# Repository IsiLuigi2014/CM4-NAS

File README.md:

# CM4 NAS Board [UNMAINTAINED | UNTESTED]

This is a fork from the CM4 NAS Board Project from mebs, added 12V power circuitry only to power it. UNTESTED

This Compute Module 4 carrier board design exposes a subset of the CM4's interfaces, including its single PCIe 2.0 lane to accept an external SATA controller card.
This design is based off of the official Raspberry Pi Foundation's CM4 IO board (the KiCad project is available on the [IO board official page](https://www.raspberrypi.org/products/compute-module-4-io-board/?resellerType=home)). Removed the IO that was less relevant for a NAS and rearranged the remaining interfaces for a smaller footprint that would fit within the width of a standard 3.5" hard drive.

The board was intentionally kept simple to limit mistakes as this is my first ever attempt at designing a PCB and I have no background in electronics, so all the power management is left to external power supplies and buck converters. It's important to use good quality regulated power supplies with this board as it offers no protection other than what is built into the CM4.

Also made 3D printed enclosure for the final product. Design available here: https://www.thingiverse.com/thing:4820662 (Properly not compertablie anymore since made board bigger for 12v power only)

Feel free to explore the discussion section of this repo to share ideas.

[Latest Reddit post here.](https://www.reddit.com/r/raspberry_pi/comments/mkbxss/cm4_custom_nas_complete/)

##### Table of Contents
- [Software](#software)
- [Board IO](#board-io)
  * [CM4 IO Breakout](#cm4-io-breakout)
  * [Other Connections on the Board](#other-connections-on-the-board)
- [PCB Assembly](#pcb-assembly)
  * [Manufacturing](#manufacturing)
  * [Required Parts](#required-parts)
  * [Building](#building)
- [Pinout](#pinout)
- [Revision History](#revision-history)

# Software
For the software part of this project, I highly recommend [Jeff Geerling's repo](https://github.com/geerlingguy/raspberry-pi-pcie-devices/issues), where he documented similar endeavors, but you will likely have to recompile the kernel after enabling some modules to be able to use a PCIe SATA controller.

Don't hesitate to ask questions in the Discussion tab of this repo.

# Board IO
## CM4 IO Breakout
The interfaces the board forwards from the CM4 are the following:
- **PCIe x1 Gen2**: Good old PCIe 2.0, nothing special about it... if not that it's on a Raspberry Pi.
- **Ethernet**: To reduce the number of components on the board and make assembly easier, a MagJack is used instead of a simple RJ45 connector. I had to look this up when I saw it in the IO board design, but a MagJack seems to be simply an RJ45 connector with integrated filters to help with signal integrity. Footprint is specific to the part listed bellow.
- **Single master/slave USB, selected with jumper**: A USB type A port to plug a keyboard, a flash drive, a hub, or whatever you want to use as a USB slave to the CM4. Footprint is not standard so make sure it fits yours if you manufacture the PCB. Can also be used in slave mode (CM4 as slave). You would use this to program the eMMC with you computer. This connection taps into the same single USB bus the CM4 has to offer, but when this is used, the VCC input from the master signals that the CM4 should behave as a slave. Currently the footprint for this is a simple 5 pin header.
- **Full size HDMI**:  Mostly for debugging purposes, hooked to the HDMI0 output of the CM4.
- **I²C**: This is marked "OLED" on the board because this was the intended use, but you can use this to slave any I²C device to the CM4. Five-pin JST connector footprint (fits simple headers too).
- **Single wire temperature sensor**: Marked "Temp_sensor" on the board, hooked to GPIO_4 on the CM4. I would recommend using it for a temp sensor near the SATA controller because they can get really hot and control the fan (see bellow) based on that.
- **9 GPIOs**: General purpose IO header, including Gnd, 3V3 and 5V pins.
- **Configuration headers**: nRPIBOOT, EEPROM_nWP, AIN1, SYNC_IN, SYNC_OUT, TV_OUT, GLOBAL_EN, RUN_PG, WL_nDis, BT_nDis. The pinout is detailed on the board.

## Other Connections on the Board
Other than relaying the compute module's IOs, the board adds other connections, mainly for power.
- **Fan control**: The board expects a dedicated PWM fan controller IC (see part list). Its output is routed to this JST connector (or your typical PWM fan connector) marked "Fan_PWM" on the board.
- **USB selection headers**: To avoid needing a USB MUX on board, this header should be used with a jumper to select if you want to use the USB bus as master or as slave.
- **HDDs power**: Labeled "SATA_PWR". This is the power rail for the hard drives.

# PCB Assembly
## Manufacturing
There is a *Fab* folder at the repo's root. This folder contains all the files that you need to order PCBs from a manufacturer. You will find in the folder a Fab_rev1.4.zip archive that is all you need to order from JLC PCB. This is the latest version and the one I have been running for months now.

## Required Parts
Other than the standard caps and resistors, here are the components you will need if you want to assemble the board:
- **High density connectors** ([digikey](https://www.digikey.ca/en/products/detail/hirose-electric-co-ltd/DF40C-100DS-0.4V%2851%29/1969495), [LCSC](https://lcsc.com/product-detail/Mezzanine-Connectors-Board-to-Board_HRS-Hirose-DF40C-100DS-0-4V-51_C597931.html)): You will need these to connect the CM4 to the board. They can be very daunting, but I found [this video](https://www.youtube.com/watch?v=eukcrFc18P4) of someone neatly soldering them with a hot air gun. When I finaly got to try it, I was surprise at how doable it was.
- **Ethernet** ([digikey](https://www.digikey.de/de/products/detail/abracon-llc/ARJM11C7-502-AB-ER2-T/7675199)): Switch from the expensive one to a cheaper model.
- **Fan controller** ([digikey](https://www.digikey.ca/en/products/detail/microchip-technology/EMC2301-1-ACZL-TR/4696431), [LCSC](https://lcsc.com/product-detail/_MICROCHIP_EMC2301-1-ACZL-TR_EMC2301-1-ACZL-TR_C148036.html)): This chip is the exact same one that is on the official IO board and it's controlled by the CM4 through I²C.
- **ESD sinks** ([digikey](https://www.digikey.ca/en/products/detail/texas-instruments/TPD4EUSB30DQAR/2503671), [LCSC](https://lcsc.com/product-detail/Diodes-ESD_Texas-Instruments-TPD4EUSB30DQAR_C90627.html)): They are optional in my (very uninformed) opinion. I think they were included on the IO board for POE applications mostly.
- **Signal buffer** ([digikey](https://www.digikey.ca/en/products/detail/diodes-incorporated/74LVC1G07SE-7/2356550), [LCSC](https://lcsc.com/product-detail/Logic-Buffers-Drivers-Receivers-Transceivers_Diodes-Incorporated-74LVC1G07SE-7_C67531.html)): Used for the power LED and to buffer RUN_PG signal to be able to wake the CM4 from a sleep state.
- **HDMI connector** ([LCSC](https://lcsc.com/product-detail/Audio-Video-Connectors_SOFNG-HDMI-019S_C111617.html)): Basic full size HDMI connector.

## Building
To build the board, you will need a soldering iron and a hot air gun (or a reflow oven). I would recommend starting with the Hirose high density connectors as they are without a doubt the hardest part. [This video](https://www.youtube.com/watch?v=eukcrFc18P4) I referred to earlier is a good starting point, it makes for a fine tutorial.
It only took a couple tries before I could get a decent result (image from microscope at around 50-60x):

Once the HD connectors are in place, you can move on to the ESD sinks. They are very small and can also be daunting, but soldering them turned out to be easier than expected.
The trick is to put as little solder paste as possible and the chips will naturally be pulled in place by the solder's surface tension.

The rest of the parts should be fairly easy to solder with a standard iron.

# Pinout
**Not up to date anymore.**

# Revision History
- **1**: Initial version
- **1.1**: Fixed wrong footprint for fan controller
- **1.2**: Changed the USB select headers for a simpler solution with a single jumper
- **1.3**: Replaced the HDMI header by a full size HDMI female connector, exposed 9 GPIOs, inverted polarity back for PCIe Tx/Rx signals and added a power LED.
- **1.4**: Add pin to OLED connector for button, use SMD caps and LEDs, more info on silkscreen and fixed some traces.
- **1.5**: Added support for 12v power only

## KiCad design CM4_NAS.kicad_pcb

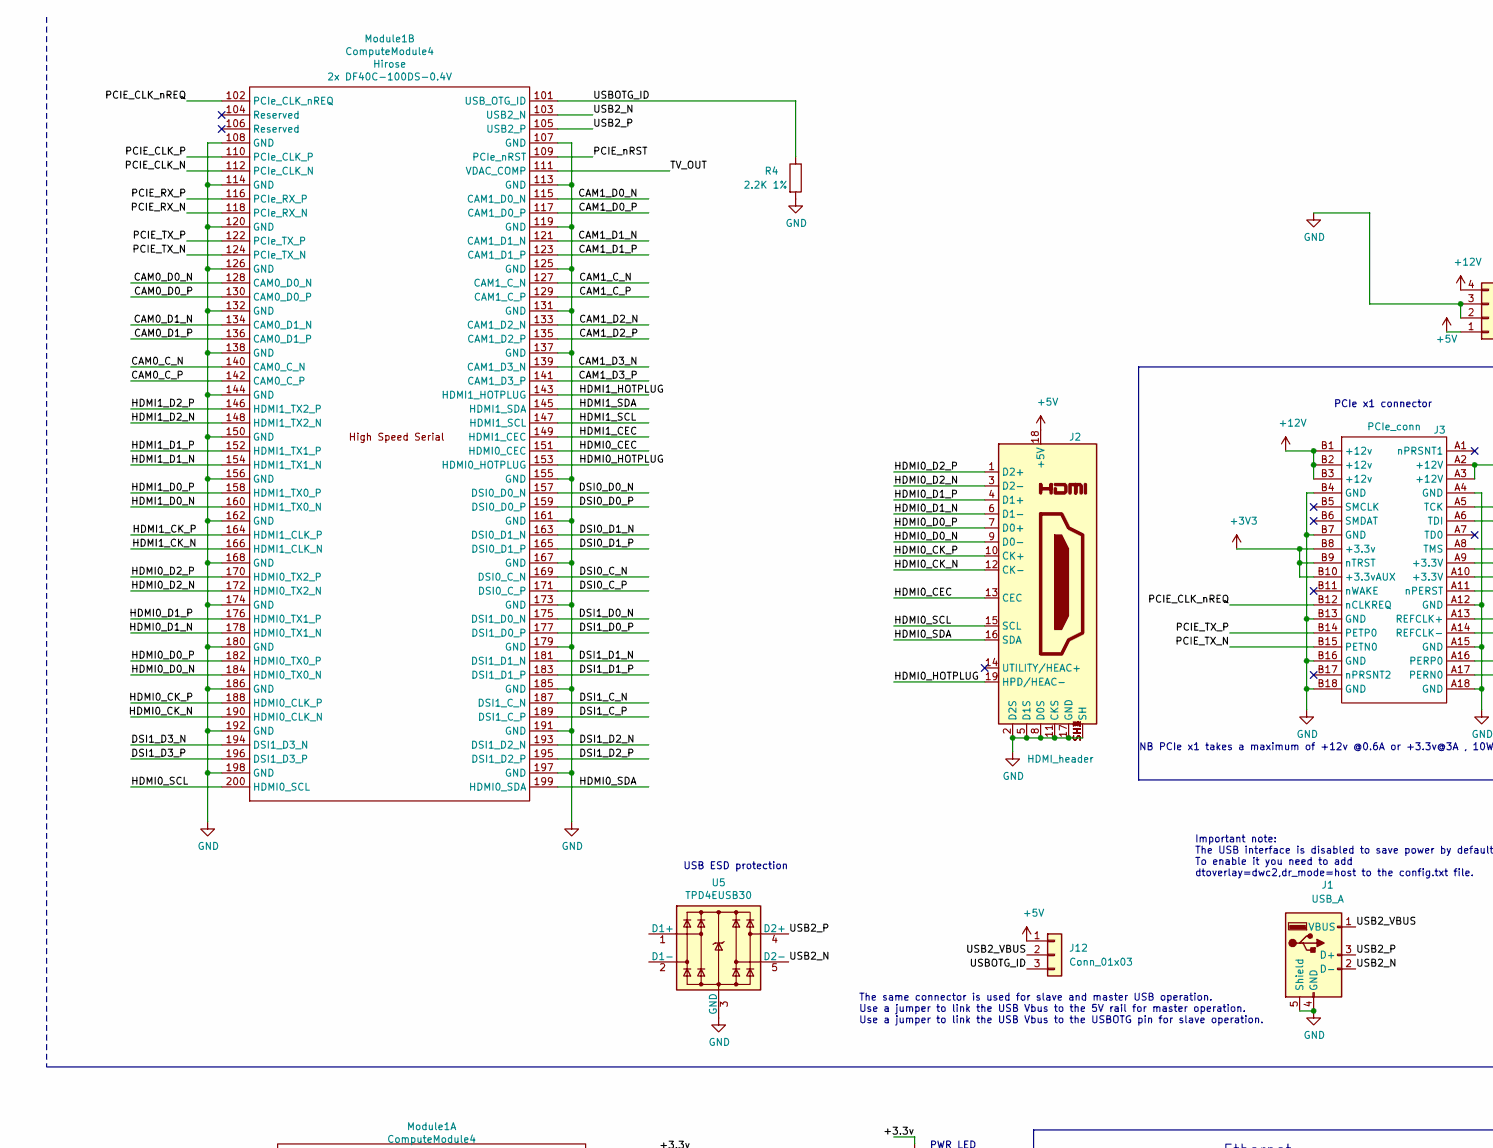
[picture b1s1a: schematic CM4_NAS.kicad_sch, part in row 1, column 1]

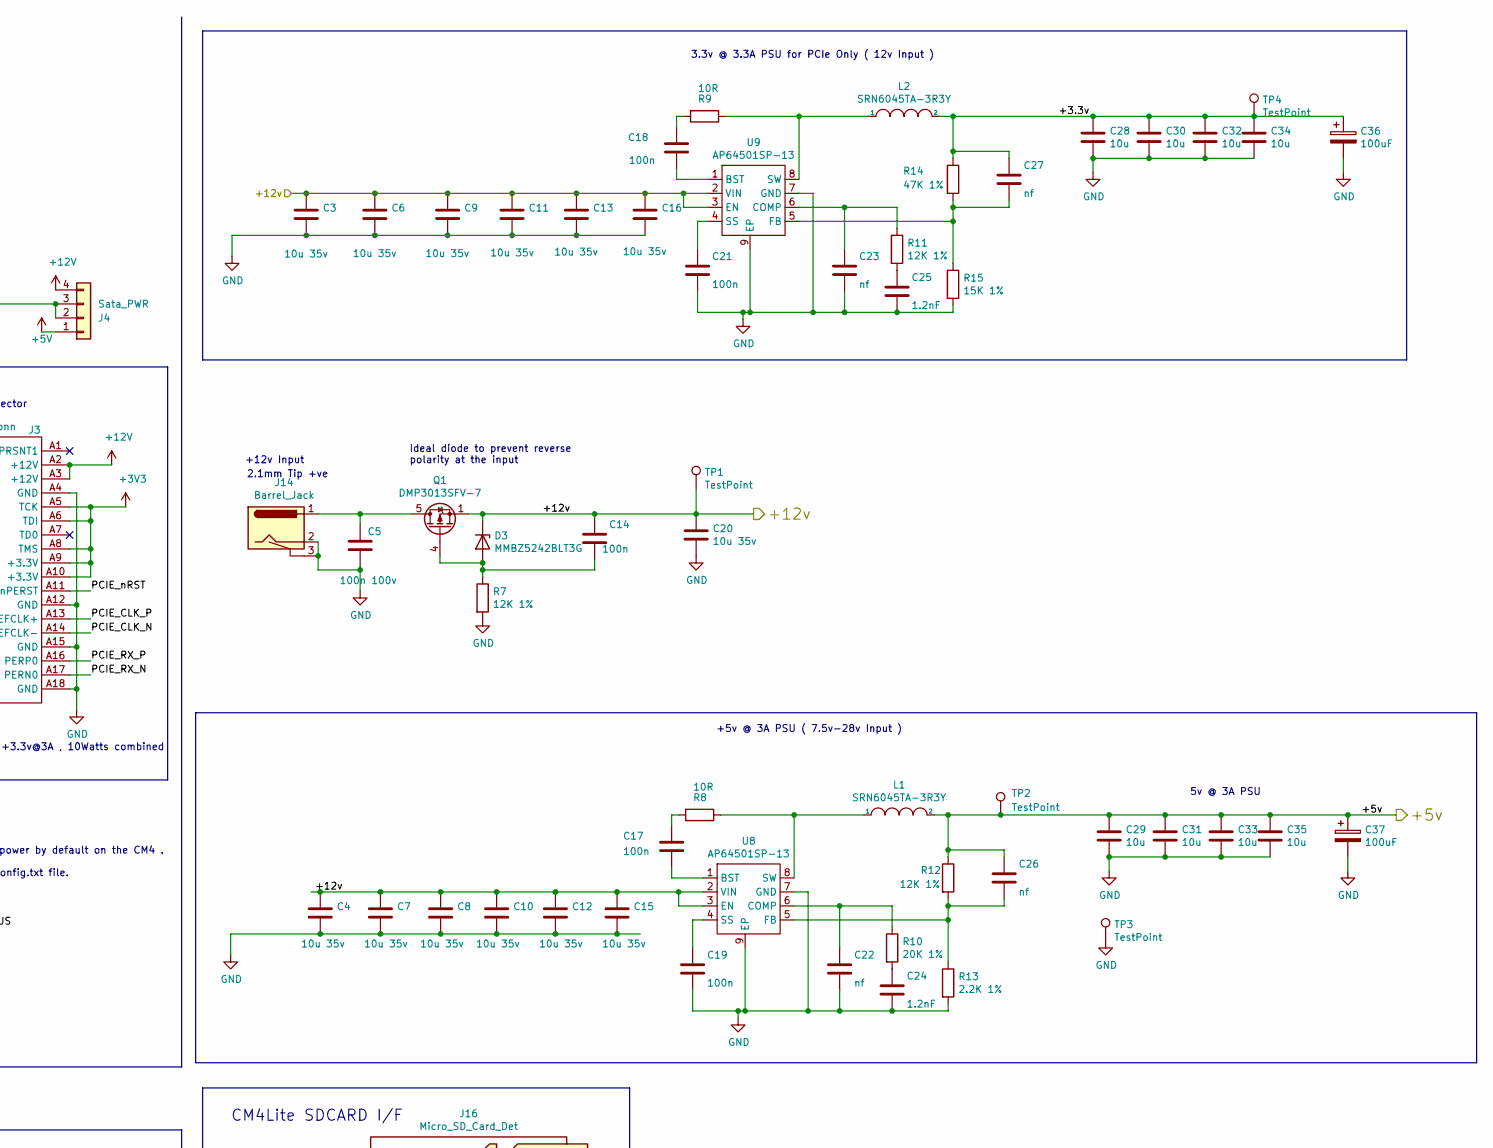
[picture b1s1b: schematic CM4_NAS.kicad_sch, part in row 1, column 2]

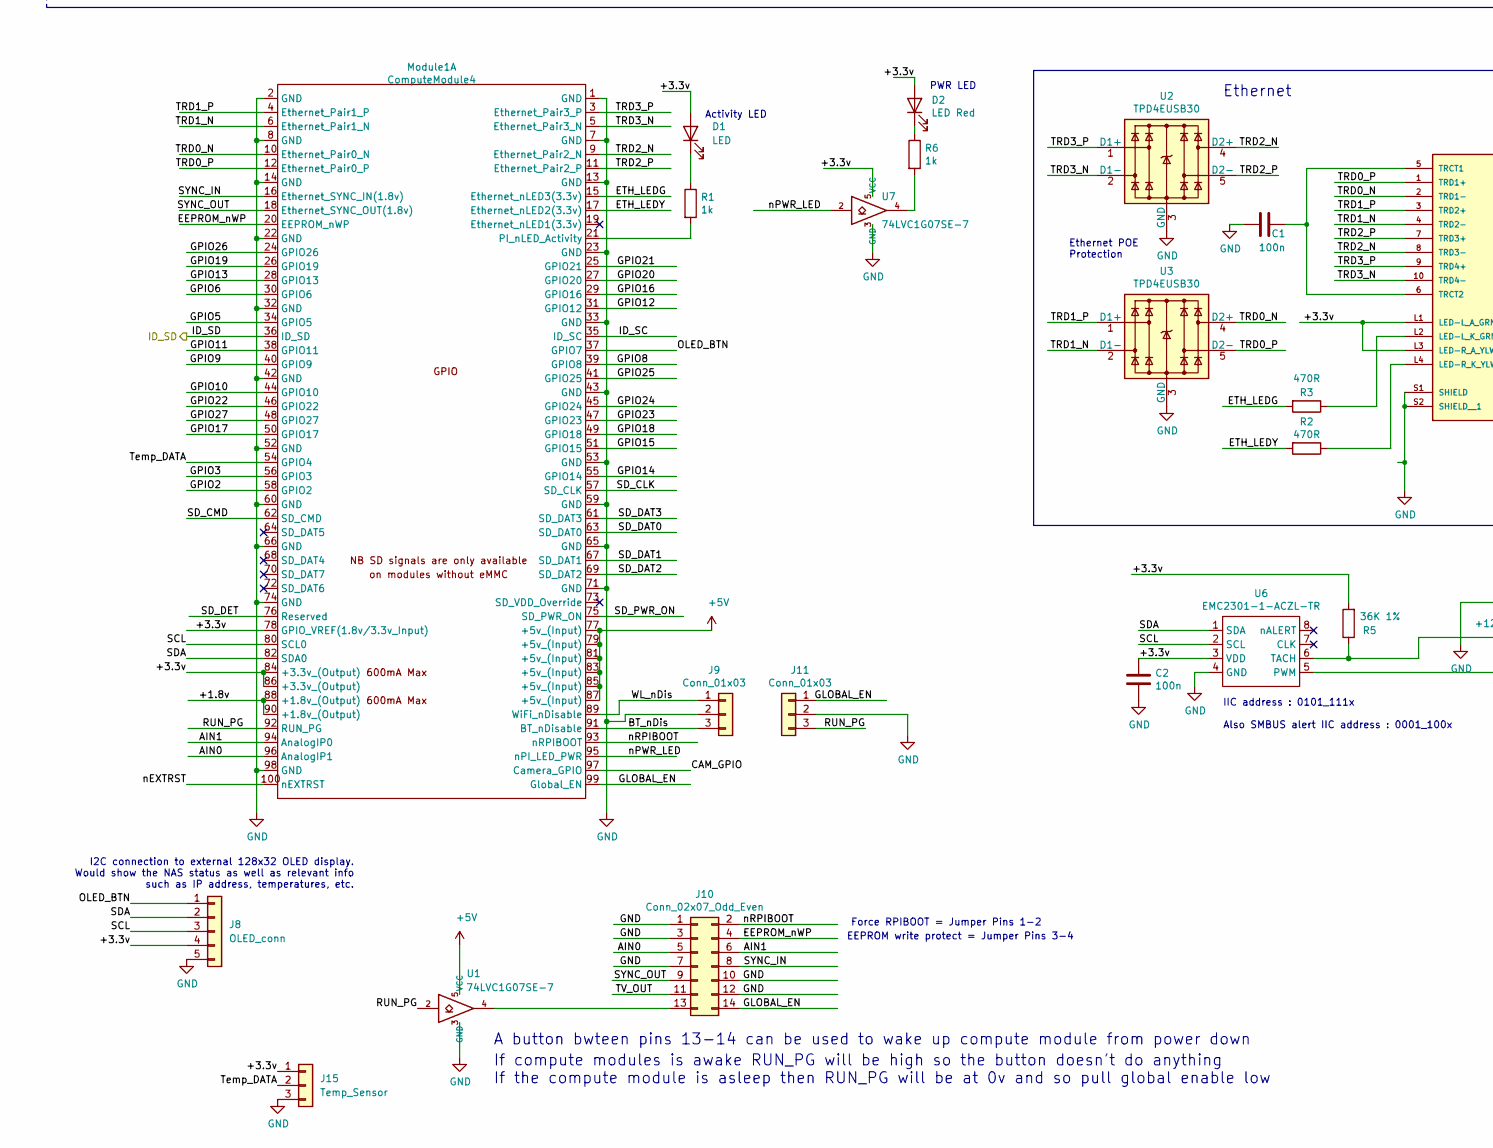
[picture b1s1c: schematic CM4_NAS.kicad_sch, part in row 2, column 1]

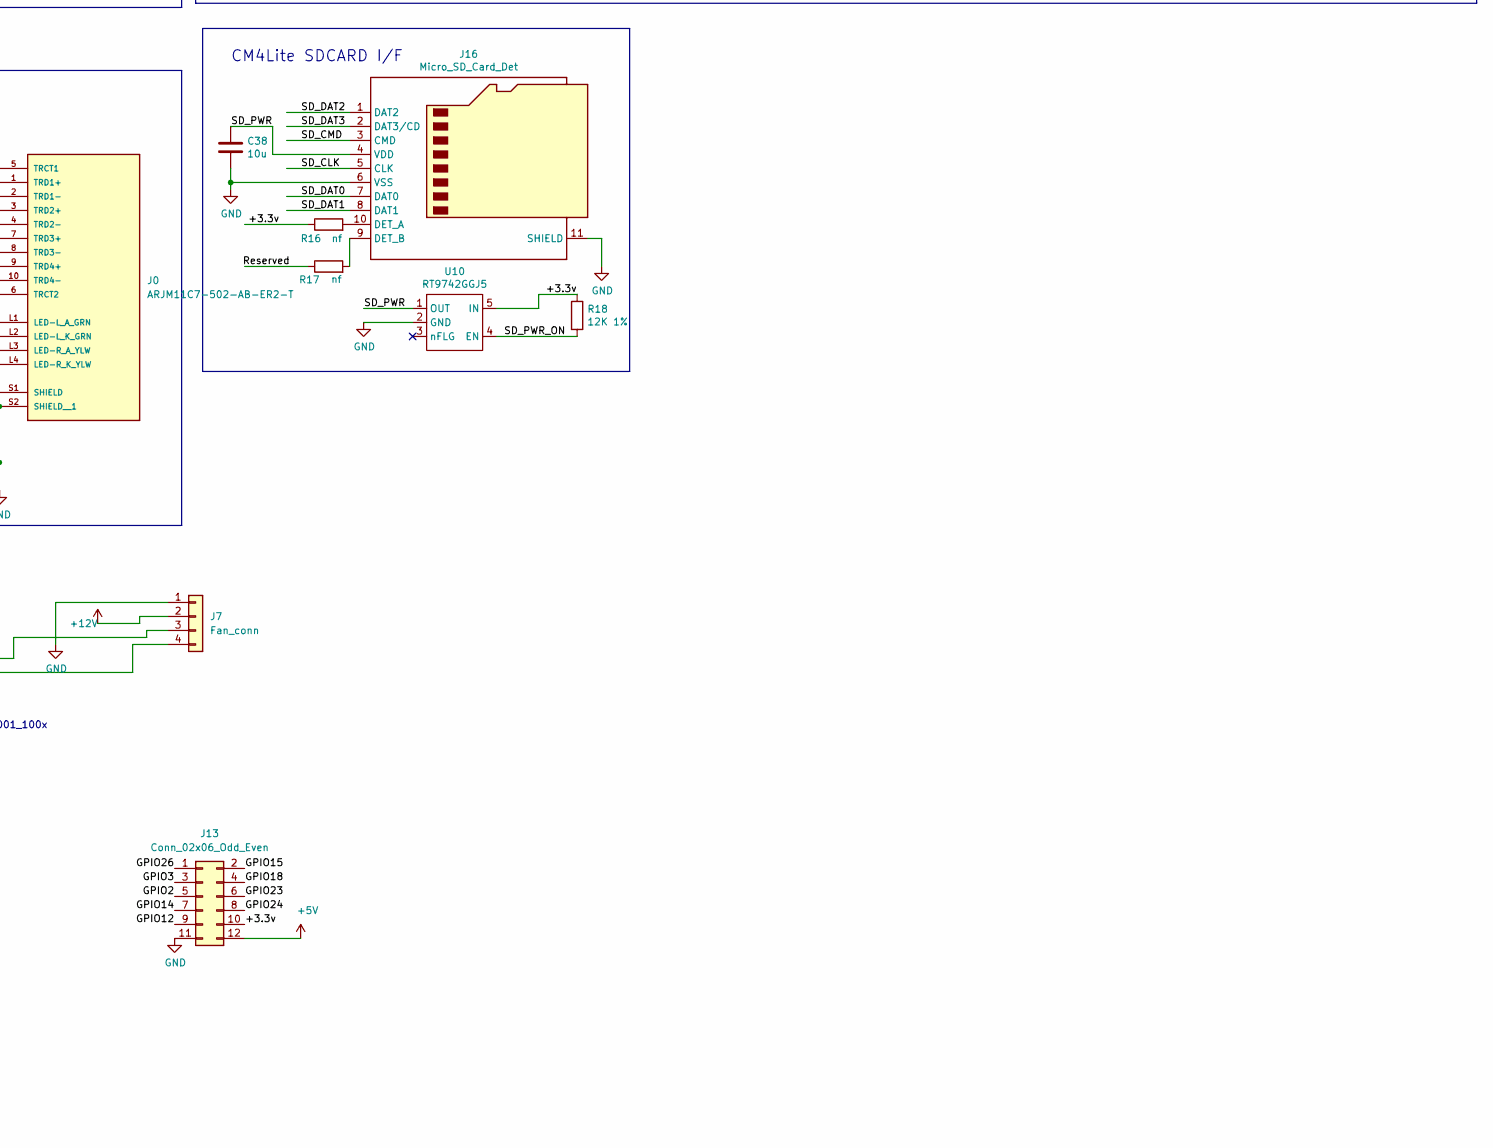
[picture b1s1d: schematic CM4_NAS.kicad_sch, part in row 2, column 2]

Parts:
C1, C2: 100n; C_0805_2012Metric_Pad1.18x1.45mm_HandSolder
C3, C4, C6, C7, C8, C9, C10, C11, C12, C13, C15, C16, C20: 10u 35v; C_0805_2012Metric; Part Description 10uF 10% or 20% 35V Ceramic Capacitor X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
C5: 100n 100v; C_0402_1005Metric; Part Description 0.1uF 10% 100V Ceramic Capacitor X5R 04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
C14, C17, C18, C19, C21: 100n; C_0402_1005Metric; Part Description 0.1uF 10% 16V Ceramic Capacitor X7R 040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
C22, C23: nf; C_0402_1005Metric
C24, C25: 1.2nF; C_0402_1005Metric; Part Description 1200pF 10% 10V Ceramic Capacitor X5R 04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
C26: nf; C_0402_1005Metric; Part Description 220 pF, 50 V, 0402 [1005 Metric], ± 5%,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
C27: nf; C_0402_1005Metric; Part Description 27pF 5% 50V Ceramic Capacitor C0G, NP0 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
C28, C29, C30, C31, C32, C33, C34, C35, C38: 10u; C_0805_2012Metric; Part Description 10uF 10% 10V Ceramic Capacitor X7R 0805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
C36, C37: 100uF; CP_EIA-7343-31_Kemet-D; Part Description Capacitor, SP-Cap, 100u, 6.3V, 15mR ESR
D1: LED; LED_0805_2012Metric_Pad1.15x1.40mm_HandSolder
D2: LED Red; LED_0805_2012Metric_Pad1.15x1.40mm_HandSolder
D3: MMBZ5242BLT3G; D_SOT-23_ANK; Part Description Zener Diode 12V 225mW 5% Surface Mount 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
J0: ARJM11C7-502-AB-ER2-T; ABRACON_ARJM11C7-502-AB-ER2-T; PARTREV 04.22.2019
J1: USB_A; USB_A_Vertical
J2: HDMI_header; HDMI EDAC 690-019-298-412
J3: PCIe_conn; PCIex1-36; Part Description PCI Express/PCI Connectors PCIE THROUGH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
J4: Sata_PWR; JST_XH_B4B-XH-A_1x04_P2.50mm_Vertical
J7: Fan_conn; JST_XH_B4B-XH-A_1x04_P2.50mm_Vertical
J8: OLED_conn; JST_XH_B5B-XH-A_1x05_P2.50mm_Vertical
J9, J11: Conn_01x03; PinHeader_1x03_P2.54mm_Vertical; Part Description 3pin 0.1" connector
J10: Conn_02x07_Odd_Even; PinHeader_2x07_P2.54mm_Vertical; Part Description PinHeader_2x07_P2.54mm_Vertical
J12: Conn_01x03; PinHeader_1x03_P2.54mm_Vertical
J13: Conn_02x06_Odd_Even; PinHeader_2x06_P2.54mm_Vertical
J14: Barrel_Jack; BarrelJack_Horizontal; Part Description DC Power Connectors PCB 2.1MM
J15: Temp_Sensor; PinSocket_1x03_P2.54mm_Vertical
J16: Micro_SD_Card_Det; SDCARD_MOLEX_503398-1892; Part Description 9 (8 + 1) Position Card Connector micro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
L1, L2: SRN6045TA-3R3Y; L_Bourns_SRN6045TA; Part Description 3.3µH Semi-Shielded Wirewound Inductor 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
Module1: ComputeModule4; Raspberry-Pi-4-Compute-Module; Part Description 100 Position Connector Receptacle, Cent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
Q1: DMP3013SFV-7; Diodes_PowerDI3333-8; Part Description DMP3013SFV-7 - Power MOSFET, P Channel,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
R1, R6: 1k; R_0402_1005Metric; Part Description Resistor 1K M1005 1% 63mW
R2: 470R; R_0402_1005Metric
R3: 470R; R_0402_1005Metric; Part Description Resistor 470R M1005 1% 63mW
R4: 2.2K 1%; R_0402_1005Metric
R5: 36K 1%; R_0402_1005Metric
R7, R11, R12, R18: 12K 1%; R_0402_1005Metric; Part Description Resistor 12K M1005 1% 63mW
R8, R9: 10R; R_0402_1005Metric; Part Description Resistor 10R M1005 1% 63mW
R10: 20K 1%; R_0402_1005Metric; Part Description Resistor 20K M1005 1% 63mW
R13: 2.2K 1%; R_0402_1005Metric; Part Description Resistor 2.2K M1005 1% 63mW
R14: 47K 1%; R_0402_1005Metric; Part Description Resistor 47K M1005 1% 63mW
R15: 15K 1%; R_0402_1005Metric; Part Description Resistor 15K M1005 1% 63mW
R16, R17: nf; R_0402_1005Metric; Part Description Resistor 1K M1005 1% 63mW
TP1, TP2, TP3, TP4: TestPoint; TestPoint_Pad_2.0x2.0mm
U1, U7: 74LVC1G07SE-7; SOT-353_SC-70-5; Part Description Buffer, Non-Inverting 1 Element 1 Bit p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
U2, U3, U5: TPD4EUSB30; USON-10_2.5x1.0mm_P0.5mm; Part Description Quad TVS diode for high speed signals (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
U6: EMC2301-1-ACZL-TR; MSOP-8_3x3mm_P0.65mm; Part Description Motor Driver PWM 8-MSOP
U8, U9: AP64501SP-13; SOIC-8-1EP_3.9x4.9mm_P1.27mm_EP2.95x4.9mm_Mask2.71x3.4mm_Th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; Part Description Buck Switching Regulator IC Positive Ad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
U10: RT9742GGJ5; SOT-23-5; Part Description Power Switch/Driver 1:1 N-Channel 1A TS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

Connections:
+3V3: J3.A5 (TCK), J3.A6 (TDI), J3.A8 (TMS), J3.A9 (+3.3V), J3.A10 (+3.3V), J3.B8 (+3.3v), J3.B9 (nTRST), J3.B10 (+3.3vAUX)
+5V: J2.18 (+5V), J4.1, J12.1, J13.12, Module1.77 (+5v_(Input)), Module1.79 (+5v_(Input)), Module1.81 (+5v_(Input)), Module1.83 (+5v_(Input)), Module1.85 (+5v_(Input)), Module1.87 (+5v_(Input)), U1.5 (VCC)
+12V: J3.A2 (+12V), J3.A3 (+12V), J3.B1 (+12v), J3.B2 (+12v), J3.B3 (+12v), J4.4, J7.2
/+1.8v: Module1.88 (+1.8v_(Output)), Module1.90 (+1.8v_(Output))
/+3.3v: C2.1, C27.1, C28.1, C30.1, C32.1, C34.1, C36.1, D1.2 (A), D2.2 (A), J0.L1 (LED-L_A_GRN), J0.L3 (LED-R_A_YLW), J8.4, J13.10, J15.1, L2.2, Module1.78 (GPIO_VREF(1.8v/3.3v_Input)), Module1.84 (+3.3v_(Output)), Module1.86 (+3.3v_(Output)), R5.2, R14.1, R16.1, R18.1, TP4.1, U6.3 (VDD), U7.5 (VCC), U10.5 (IN)
/+5v: C26.1, C29.1, C31.1, C33.1, C35.1, C37.1, L1.2, R12.1, TP2.1
/+12v: C3.1, C4.1, C6.1, C7.1, C8.1, C9.1, C10.1, C11.1, C12.1, C13.1, C14.1, C15.1, C16.1, C20.1, D3.1 (K), Q1.1 (S), Q1.2 (S), Q1.3 (S), TP1.1, U8.2 (VIN), U8.3 (EN), U9.2 (VIN), U9.3 (EN)
/AIN0: J10.5, Module1.96 (AnalogIP1)
/AIN1: J10.6, Module1.94 (AnalogIP0)
/BT_nDis: J9.3, Module1.91 (BT_nDisable)
/CAM0_C_N: Module1.140 (CAM0_C_N)
/CAM0_C_P: Module1.142 (CAM0_C_P)
/CAM0_D0_N: Module1.128 (CAM0_D0_N)
/CAM0_D0_P: Module1.130 (CAM0_D0_P)
/CAM0_D1_N: Module1.134 (CAM0_D1_N)
/CAM0_D1_P: Module1.136 (CAM0_D1_P)
/CAM1_C_N: Module1.127 (CAM1_C_N)
/CAM1_C_P: Module1.129 (CAM1_C_P)
/CAM1_D0_N: Module1.115 (CAM1_D0_N)
/CAM1_D0_P: Module1.117 (CAM1_D0_P)
/CAM1_D1_N: Module1.121 (CAM1_D1_N)
/CAM1_D1_P: Module1.123 (CAM1_D1_P)
/CAM1_D2_N: Module1.133 (CAM1_D2_N)
/CAM1_D2_P: Module1.135 (CAM1_D2_P)
/CAM1_D3_N: Module1.139 (CAM1_D3_N)
/CAM1_D3_P: Module1.141 (CAM1_D3_P)
/CAM_GPIO: Module1.97 (Camera_GPIO)
/DSI0_C_N: Module1.169 (DSI0_C_N)
/DSI0_C_P: Module1.171 (DSI0_C_P)
/DSI0_D0_N: Module1.157 (DSI0_D0_N)
/DSI0_D0_P: Module1.159 (DSI0_D0_P)
/DSI0_D1_N: Module1.163 (DSI0_D1_N)
/DSI0_D1_P: Module1.165 (DSI0_D1_P)
/DSI1_C_N: Module1.187 (DSI1_C_N)
/DSI1_C_P: Module1.189 (DSI1_C_P)
/DSI1_D0_N: Module1.175 (DSI1_D0_N)
/DSI1_D0_P: Module1.177 (DSI1_D0_P)
/DSI1_D1_N: Module1.181 (DSI1_D1_N)
/DSI1_D1_P: Module1.183 (DSI1_D1_P)
/DSI1_D2_N: Module1.193 (DSI1_D2_N)
/DSI1_D2_P: Module1.195 (DSI1_D2_P)
/DSI1_D3_N: Module1.194 (DSI1_D3_N)
/DSI1_D3_P: Module1.196 (DSI1_D3_P)
/EEPROM_nWP: J10.4, Module1.20 (EEPROM_nWP)
/ETH_LEDG: Module1.15 (Ethernet_nLED3(3.3v)), R3.2
/ETH_LEDY: Module1.17 (Ethernet_nLED2(3.3v)), R2.2
/GLOBAL_EN: J10.14, J11.1, Module1.99 (Global_EN)
/GPIO2: J13.5, Module1.58 (GPIO2)
/GPIO3: J13.3, Module1.56 (GPIO3)
/GPIO5: Module1.34 (GPIO5)
/GPIO6: Module1.30 (GPIO6)
/GPIO8: Module1.39 (GPIO8)
/GPIO9: Module1.40 (GPIO9)
/GPIO10: Module1.44 (GPIO10)
/GPIO11: Module1.38 (GPIO11)
/GPIO12: J13.9, Module1.31 (GPIO12)
/GPIO13: Module1.28 (GPIO13)
/GPIO14: J13.7, Module1.55 (GPIO14)
/GPIO15: J13.2, Module1.51 (GPIO15)
/GPIO16: Module1.29 (GPIO16)
/GPIO17: Module1.50 (GPIO17)
/GPIO18: J13.4, Module1.49 (GPIO18)
/GPIO19: Module1.26 (GPIO19)
/GPIO20: Module1.27 (GPIO20)
/GPIO21: Module1.25 (GPIO21)
/GPIO22: Module1.46 (GPIO22)
/GPIO23: J13.6, Module1.47 (GPIO23)
/GPIO24: J13.8, Module1.45 (GPIO24)
/GPIO25: Module1.41 (GPIO25)
/GPIO26: J13.1, Module1.24 (GPIO26)
/GPIO27: Module1.48 (GPIO27)
/HDMI0_CEC: J2.13 (CEC), Module1.151 (HDMI0_CEC)
/HDMI0_CK_N: J2.12 (CK-), Module1.190 (HDMI0_CLK_N)
/HDMI0_CK_P: J2.10 (CK+), Module1.188 (HDMI0_CLK_P)
/HDMI0_D0_N: J2.9 (D0-), Module1.184 (HDMI0_TX0_N)
/HDMI0_D0_P: J2.7 (D0+), Module1.182 (HDMI0_TX0_P)
/HDMI0_D1_N: J2.6 (D1-), Module1.178 (HDMI0_TX1_N)
/HDMI0_D1_P: J2.4 (D1+), Module1.176 (HDMI0_TX1_P)
/HDMI0_D2_N: J2.3 (D2-), Module1.172 (HDMI0_TX2_N)
/HDMI0_D2_P: J2.1 (D2+), Module1.170 (HDMI0_TX2_P)
/HDMI0_HOTPLUG: J2.19 (HPD/HEAC-), Module1.153 (HDMI0_HOTPLUG)
/HDMI0_SCL: J2.15 (SCL), Module1.200 (HDMI0_SCL)
/HDMI0_SDA: J2.16 (SDA), Module1.199 (HDMI0_SDA)
/HDMI1_CEC: Module1.149 (HDMI1_CEC)
/HDMI1_CK_N: Module1.166 (HDMI1_CLK_N)
/HDMI1_CK_P: Module1.164 (HDMI1_CLK_P)
/HDMI1_D0_N: Module1.160 (HDMI1_TX0_N)
/HDMI1_D0_P: Module1.158 (HDMI1_TX0_P)
/HDMI1_D1_N: Module1.154 (HDMI1_TX1_N)
/HDMI1_D1_P: Module1.152 (HDMI1_TX1_P)
/HDMI1_D2_N: Module1.148 (HDMI1_TX2_N)
/HDMI1_D2_P: Module1.146 (HDMI1_TX2_P)
/HDMI1_HOTPLUG: Module1.143 (HDMI1_HOTPLUG)
/HDMI1_SCL: Module1.147 (HDMI1_SCL)
/HDMI1_SDA: Module1.145 (HDMI1_SDA)
/ID_SC: Module1.35 (ID_SC)
/ID_SD: Module1.36 (ID_SD)
/OLED_BTN: J8.1, Module1.37 (GPIO7)
/PCIE_CLK_N: J3.A14 (REFCLK-), Module1.112 (PCIe_CLK_N)
/PCIE_CLK_P: J3.A13 (REFCLK+), Module1.110 (PCIe_CLK_P)
/PCIE_CLK_nREQ: J3.B12 (nCLKREQ), Module1.102 (PCIe_CLK_nREQ)
/PCIE_RX_N: J3.A17 (PERN0), Module1.118 (PCIe_RX_N)
/PCIE_RX_P: J3.A16 (PERP0), Module1.116 (PCIe_RX_P)
/PCIE_TX_N: J3.B15 (PETN0), Module1.124 (PCIe_TX_N)
/PCIE_TX_P: J3.B14 (PETP0), Module1.122 (PCIe_TX_P)
/PCIE_nRST: J3.A11 (nPERST), Module1.109 (PCIe_nRST)
/RUN_PG: J11.3, Module1.92 (RUN_PG), U1.2
/SCL: J8.3, Module1.80 (SCL0), U6.2 (SCL)
/SDA: J8.2, Module1.82 (SDA0), U6.1 (SDA)
/SD_CLK: J16.5 (CLK), Module1.57 (SD_CLK)
/SD_CMD: J16.3 (CMD), Module1.62 (SD_CMD)
/SD_DAT0: J16.7 (DAT0), Module1.63 (SD_DAT0)
/SD_DAT1: J16.8 (DAT1), Module1.67 (SD_DAT1)
/SD_DAT2: J16.1 (DAT2), Module1.69 (SD_DAT2)
/SD_DAT3: J16.2 (DAT3/CD), Module1.61 (SD_DAT3)
/SD_DET: Module1.76 (Reserved)
/SD_PWR_ON: Module1.75 (SD_PWR_ON), R18.2, U10.4 (EN)
/SYNC_IN: J10.8, Module1.16 (Ethernet_SYNC_IN(1.8v))
/SYNC_OUT: J10.9, Module1.18 (Ethernet_SYNC_OUT(1.8v))
/TRD0_N: J0.2 (TRD1-), Module1.10 (Ethernet_Pair0_N), U3.4 (D2+), U3.7
/TRD0_P: J0.1 (TRD1+), Module1.12 (Ethernet_Pair0_P), U3.5 (D2-), U3.6
/TRD1_N: J0.4 (TRD2-), Module1.6 (Ethernet_Pair1_N), U3.2 (D1-), U3.9
/TRD1_P: J0.3 (TRD2+), Module1.4 (Ethernet_Pair1_P), U3.1 (D1+), U3.10
/TRD2_N: J0.8 (TRD3-), Module1.9 (Ethernet_Pair2_N), U2.4 (D2+), U2.7
/TRD2_P: J0.7 (TRD3+), Module1.11 (Ethernet_Pair2_P), U2.5 (D2-), U2.6
/TRD3_N: J0.10 (TRD4-), Module1.5 (Ethernet_Pair3_N), U2.2 (D1-), U2.9
/TRD3_P: J0.9 (TRD4+), Module1.3 (Ethernet_Pair3_P), U2.1 (D1+), U2.10
/TV_OUT: J10.11, Module1.111 (VDAC_COMP)
/Temp_DATA: J15.2, Module1.54 (GPIO4)
/USB2_N: J1.2 (D-), Module1.103 (USB2_N), U5.5 (D2-), U5.6
/USB2_P: J1.3 (D+), Module1.105 (USB2_P), U5.4 (D2+), U5.7
/USB2_VBUS: J1.1 (VBUS), J12.2
/USBOTG_ID: J12.3, Module1.101 (USB_OTG_ID), R4.1
/WL_nDis: J9.1, Module1.89 (WiFi_nDisable)
/nEXTRST: Module1.100 (nEXTRST)
/nPWR_LED: Module1.95 (nPI_LED_PWR), U7.2
/nRPIBOOT: J10.2, Module1.93 (nRPIBOOT)
GND: C1.2, C2.2, C3.2, C4.2, C5.2, C6.2, C7.2, C8.2, C9.2, C10.2, C11.2, C12.2, C13.2, C15.2, C16.2, C19.2, C20.2, C21.2, C22.2, C23.2, C24.2, C25.2, C28.2, C29.2, C30.2, C31.2, C32.2, C33.2, C34.2, C35.2, C36.2, C37.2, C38.2, J0.S1 (SHIELD), J0.S2 (SHIELD__1), J1.4 (GND), J1.5 (Shield), J2.2 (D2S), J2.5 (D1S), J2.8 (D0S), J2.11 (CKS), J2.17 (GND), J2.SH1 (SH), J2.SH2 (SH), J2.SH3 (SH), J2.SH4 (SH), J3.A4 (GND), J3.A12 (GND), J3.A15 (GND), J3.A18 (GND), J3.B4 (GND), J3.B7 (GND), J3.B13 (GND), J3.B16 (GND), J3.B18 (GND), J4.2, J4.3, J7.1, J8.5, J9.2, J10.1, J10.3, J10.7, J10.10, J10.12, J11.2, J13.11, J14.2, J14.3, J15.3, J16.6 (VSS), J16.11 (SHIELD), Module1.1 (GND), Module1.2 (GND), Module1.7 (GND), Module1.8 (GND), Module1.13 (GND), Module1.14 (GND), Module1.22 (GND), Module1.23 (GND), Module1.32 (GND), Module1.33 (GND), Module1.42 (GND), Module1.43 (GND), Module1.52 (GND), Module1.53 (GND), Module1.59 (GND), Module1.60 (GND), Module1.65 (GND), Module1.66 (GND), Module1.71 (GND), Module1.74 (GND), Module1.98 (GND), Module1.107 (GND), Module1.108 (GND), Module1.113 (GND), Module1.114 (GND), Module1.119 (GND), Module1.120 (GND), Module1.125 (GND), Module1.126 (GND), Module1.131 (GND), Module1.132 (GND), Module1.137 (GND), Module1.138 (GND), Module1.144 (GND), Module1.150 (GND), Module1.155 (GND), Module1.156 (GND), Module1.161 (GND), Module1.162 (GND), Module1.167 (GND), Module1.168 (GND), Module1.173 (GND), Module1.174 (GND), Module1.179 (GND), Module1.180 (GND), Module1.185 (GND), Module1.186 (GND), Module1.191 (GND), Module1.192 (GND), Module1.197 (GND), Module1.198 (GND), R4.2, R7.2, R13.2, R15.2, TP3.1, U1.3 (GND), U2.3 (GND), U2.8 (GND), U3.3 (GND), U3.8 (GND), U5.3 (GND), U5.8 (GND), U6.4 (GND), U7.3 (GND), U8.7 (GND), U8.9 (EP), U9.7 (GND), U9.9 (EP), U10.2 (GND)
unnamed: C17.1, R8.2
unnamed: C18.1, R9.2
unnamed: C24.1, R10.2
unnamed: C25.1, R11.2
unnamed: C38.1, J16.4 (VDD), U10.1 (OUT)
unnamed: D1.1 (K), R1.1
unnamed: D2.1 (K), R6.1
unnamed: C14.2, D3.2 (A), Q1.4 (G), R7.1
unnamed: J0.L2 (LED-L_K_GRN), R3.1
unnamed: J0.L4 (LED-R_K_YLW), R2.1
unnamed: C1.1, J0.5 (TRCT1), J0.6 (TRCT2)
unnamed: J7.3, R5.1, U6.6 (TACH)
unnamed: J7.4, U6.5 (PWM)
unnamed: J10.13, U1.4
unnamed: J16.9 (DET_B), R17.2
unnamed: J16.10 (DET_A), R16.2
unnamed: Module1.21 (PI_nLED_Activity), R1.2
unnamed: C5.1, J14.1, Q1.5 (D)
unnamed: R6.2, U7.4
unnamed: U5.1 (D1+), U5.10
unnamed: U5.2 (D1-), U5.9
unnamed: C17.2, U8.1 (BST)
unnamed: C22.1, R10.1, U8.6 (COMP)
unnamed: C26.2, R12.2, R13.1, U8.5 (FB)
unnamed: C19.1, U8.4 (SS)
unnamed: L1.1, R8.1, U8.8 (SW)
unnamed: C18.2, U9.1 (BST)
unnamed: C23.1, R11.1, U9.6 (COMP)
unnamed: C27.2, R14.2, R15.1, U9.5 (FB)
unnamed: C21.1, U9.4 (SS)
unnamed: L2.1, R9.1, U9.8 (SW)

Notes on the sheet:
5v @ 3A PSU
+5v @ 3A PSU ( 7.5v-28v Input )
A button bwteen pins 13-14 can be used to wake up compute module from power down
Force RPIBOOT = Jumper Pins 1-2
CM4Lite SDCARD I/F
I2C connection to external 128x32 OLED display. Would show the NAS status as well as relevant info such as IP address, temperatures, etc.
The same connector is used for slave and master USB operation. Use a jumper to link the USB Vbus to the 5V rail for master operation. Use a jumper to link the USB Vbus to the USBOTG pin for slave operation.
Ethernet POE Protection
USB ESD protection
IIC address : 0101_111x
If compute modules is awake RUN_PG will be high so the button doesn't do anything If the compute module is asleep then RUN_PG will be at 0v and so pull global enable low
NB PCIe x1 takes a maximum of +12v @0.6A or +3.3v@3A , 10Watts combined
PWR LED
EEPROM write protect = Jumper Pins 3-4
PCIe x1 connector
3.3v @ 3.3A PSU for PCIe Only ( 12v Input )
Also SMBUS alert IIC address : 0001_100x
2.1mm Tip +ve
Activity LED
Important note: The USB interface is disabled to save power by default on the CM4 . To enable it you need to add dtoverlay=dwc2,dr_mode=host to the config.txt file.
Ethernet
+12v Input
Ideal diode to prevent reverse polarity at the input

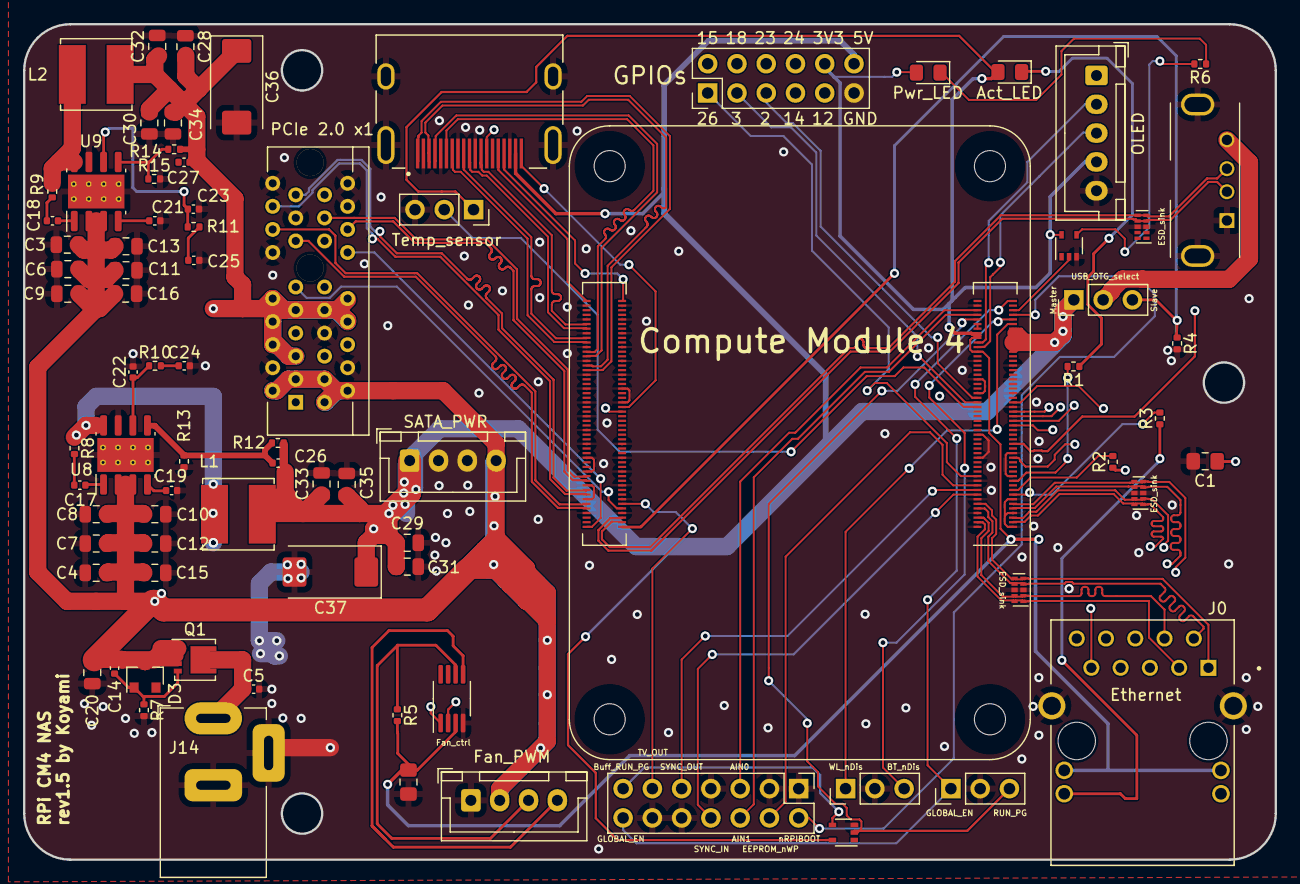
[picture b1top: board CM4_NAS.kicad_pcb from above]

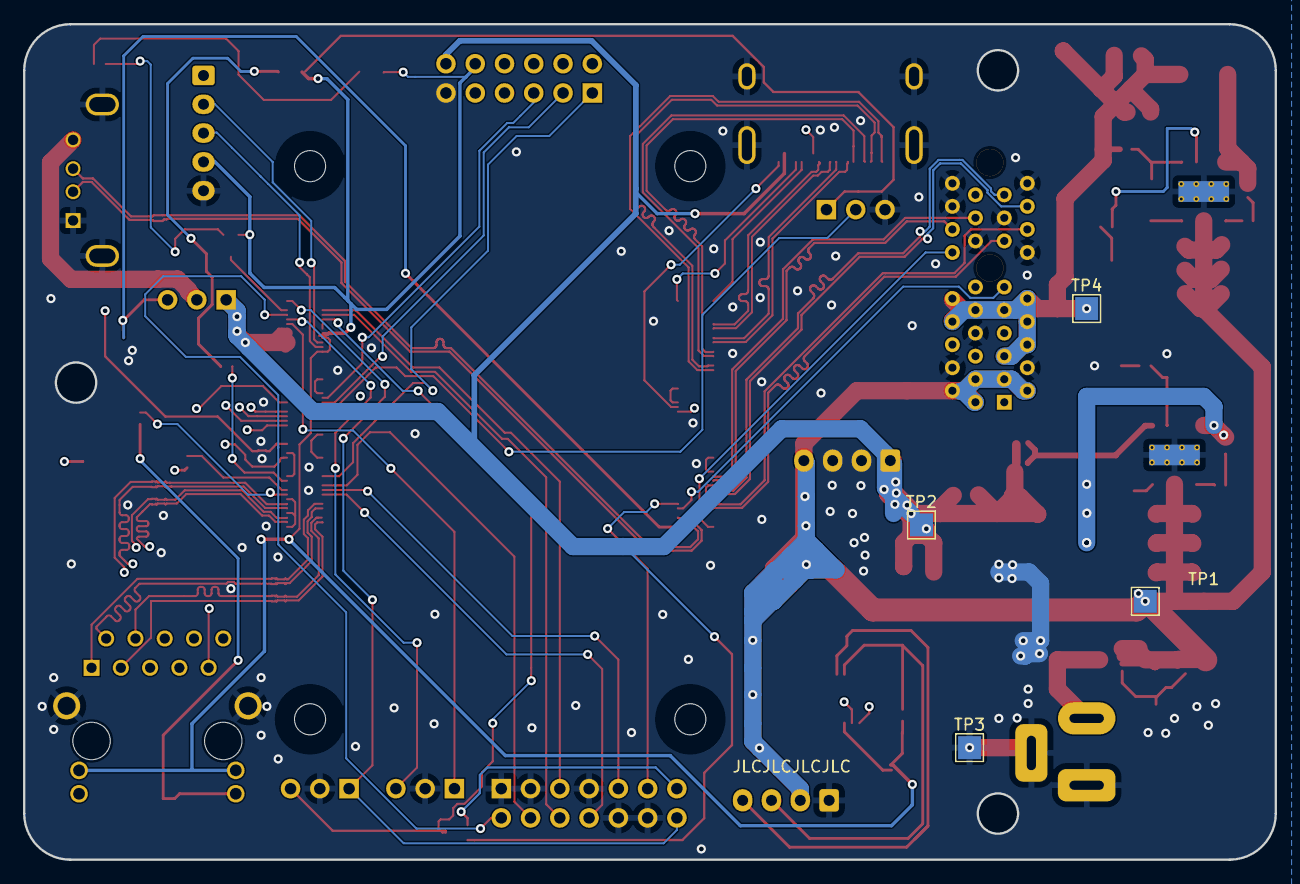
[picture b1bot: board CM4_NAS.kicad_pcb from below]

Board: 4 copper layers, 108.6 x 72.5 mm, 85 parts (4 on the bottom side), 95 nets.

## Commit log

2024-05-20 Updated to Version 1.5, imported power circuitry for 12V input only
2024-05-20 Updated README and deleted some stuff
2024-05-20 Update README.md
    Replaced Picture and edit some stuff
2024-05-20 Removed not needed files
